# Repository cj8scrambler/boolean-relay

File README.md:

# Boolean Relay

Boolean relay is a solid state relay with mutliple inputs.  It's designed for use in a 12V automotive system.  The 12V input is relayed to the output depending on the X, Y and Z inputs.  The logic controlling the output is: (X AND Y) OR ((NOT X) AND Z).  However, it can be used for more common inputs (see below).

## Design 

### Block Diagram

### Design files
- [schematic PDF](hw/schematic_v6.0.pdf) 
- [layout PDF](hw/layout_v6.0.pdf).
- [schematic KiCad](hw/bool2.kicad_sch) 
- [layout KiCad](hw/bool2.kicad_pcb)

## Configurations

### Without diodes placed
This is the normal configuration.  In this setup, the 12V output line will be powered by the 12V input line.  There is no (well, really close to no) load on the X, Y and Z inputs.

### With diodes placed
The only good use for this is if you want a boolean type control, you don't have a separate 12V input power available and the inputs are capable of driving the output.

If the 3 diodes are placed on the board, then the 12V input power is not required.  The power to drive the output will come from some combination of the input signas (X, Y and/or Z).  It's impossible to say which input will provide the power.

## Uses

### AND 2 Inputs (XY)
**Setup**: None

**Inputs**: X and Y

**Output**: On if both X and Y inputs are on

### OR 2 Inputs (X+Z)
**Setup**: Tie Y input to 12V

**Inputs**: X and Z

**Output**: On if either X or Z input is on

### NOT 1 Input (!X)
**Setup**: Tie Z input to 12V

**Inputs**: X

**Output**: On if X is off, Off if X is on

### Buffer 1 Input (X)
**Setup**: Tie Y input to 12V

**Inputs**: X

**Output**: On if X is on, Off if X is off

### XY + !XZ
**Setup**: None

**Inputs**: X, Y & Z

**Output**: If X is on, output follows Y, if X is off, output follows Z

## Assembly

I use KiCad to generate an [SVG](img/bool2-F_Paste.svg) of the paste layer.  I use a GlowForge to cut a 5 mil peice of mylar for use as a solder mask.  I can then wipe solder paste onto the board, hand place the components, then run it through a T962 reflow oven.

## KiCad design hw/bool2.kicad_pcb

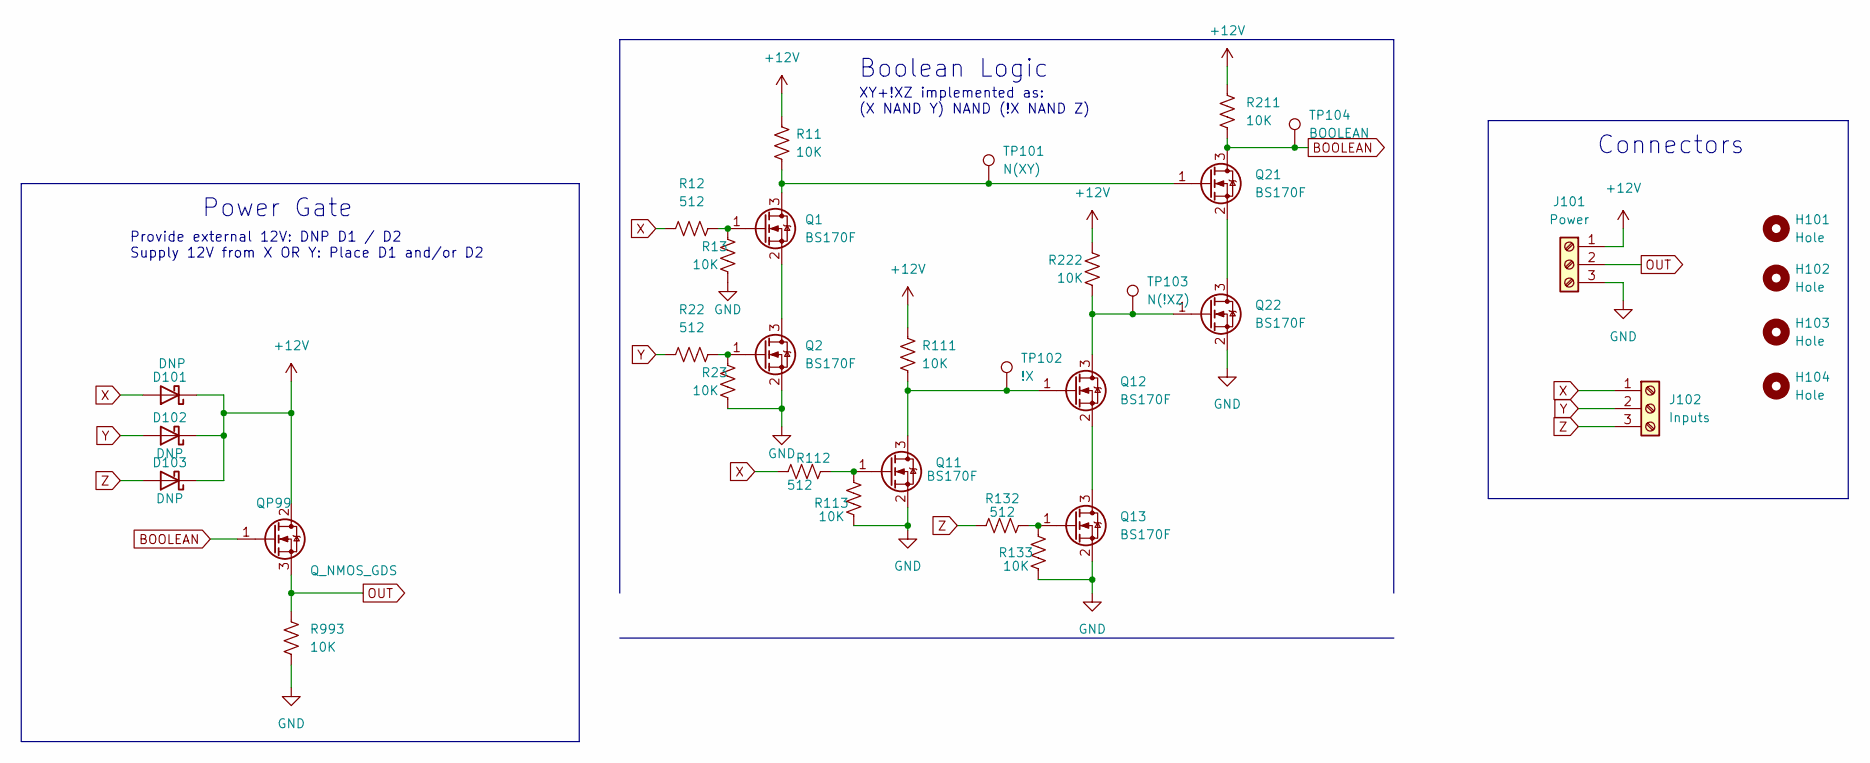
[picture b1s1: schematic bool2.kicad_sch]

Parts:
D101, D102, D103: DNP; D_DO-35_SOD27_P7.62mm_Horizontal
H101, H102, H103, H104: Hole; MountingHole_3.2mm_M3
J101: Power; TerminalBlock_Altech_AK300-3_P5.00mm
J102: Inputs; TerminalBlock_Altech_AK300-3_P5.00mm
Q1, Q2, Q11, Q12, Q13, Q21, Q22: BS170F; SOT-23
QP99: Q_NMOS_GDS; TO-220-3_Vertical
R11, R13, R23, R111, R113, R133, R211, R222, R993: 10K; R_0603_1608Metric
R12, R22, R112, R132: 512; R_0603_1608Metric
TP101: N(XY); TestPoint_Pad_D1.0mm
TP102: !X; TestPoint_Pad_D1.0mm
TP103: N(!XZ); TestPoint_Pad_D1.0mm
TP104: BOOLEAN; TestPoint_Pad_D1.0mm

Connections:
+12V: D101.1 (K), D102.1 (K), D103.1 (K), J101.1, QP99.2 (D), R11.1, R111.1, R211.1, R222.1
BOOLEAN: Q21.3 (D), QP99.1 (G), R211.2, TP104.1
GND: J101.3, Q2.2 (S), Q11.2 (S), Q13.2 (S), Q22.2 (S), R13.2, R23.2, R113.2, R133.2, R993.2
unnamed: Q1.1 (G), R12.2, R13.1
unnamed: Q1.3 (D), Q21.1 (G), R11.2, TP101.1
unnamed: Q2.1 (G), R22.2, R23.1
unnamed: Q1.2 (S), Q2.3 (D)
unnamed: Q11.1 (G), R112.2, R113.1
unnamed: Q11.3 (D), Q12.1 (G), R111.2, TP102.1
unnamed: Q12.2 (S), Q13.3 (D)
unnamed: Q12.3 (D), Q22.1 (G), R222.2, TP103.1
unnamed: Q13.1 (G), R132.2, R133.1
unnamed: Q21.2 (S), Q22.3 (D)
OUT: J101.2, QP99.3 (S), R993.1
X: D101.2 (A), J102.1, R12.1, R112.1
Y: D102.2 (A), J102.2, R22.1
Z: D103.2 (A), J102.3, R132.1

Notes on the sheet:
Power Gate
XY+!XZ implemented as: (X NAND Y) NAND (!X NAND Z)
Connectors
Boolean Logic
Provide external 12V: DNP D1 / D2 Supply 12V from X OR Y: Place D1 and/or D2

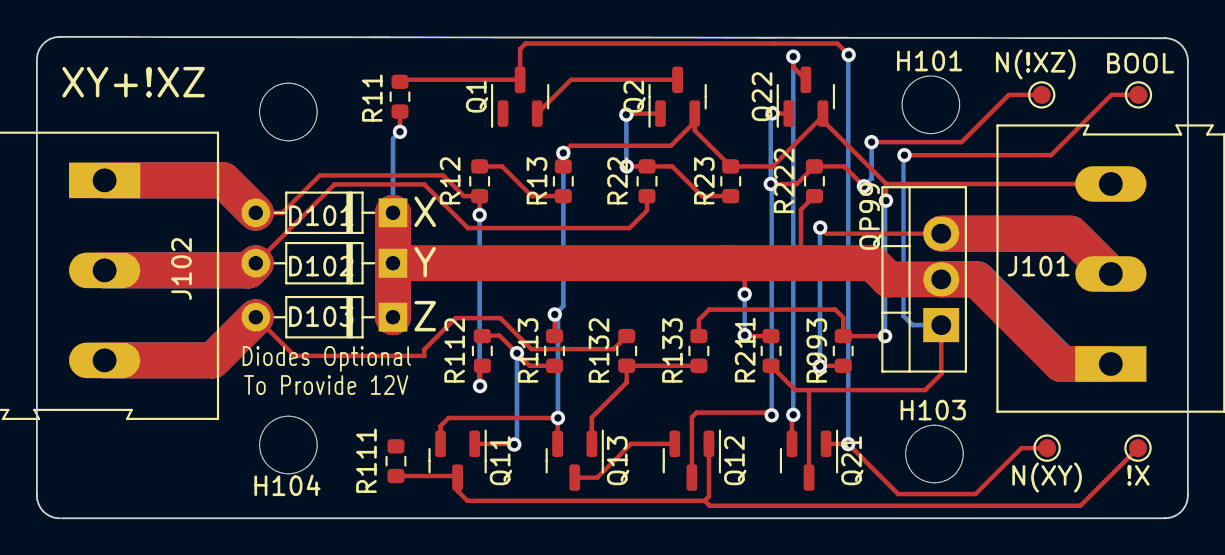
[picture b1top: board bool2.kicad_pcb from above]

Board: 2 copper layers, 63.9 x 26.7 mm, 34 parts (0 on the bottom side), 17 nets.

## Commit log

2022-12-13 Boolean Relay V6.0
    Create some documentation for Boolean Relay starting on V6.0
